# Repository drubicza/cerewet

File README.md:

# cerewet
Sound detector using LM358 Op-Amp

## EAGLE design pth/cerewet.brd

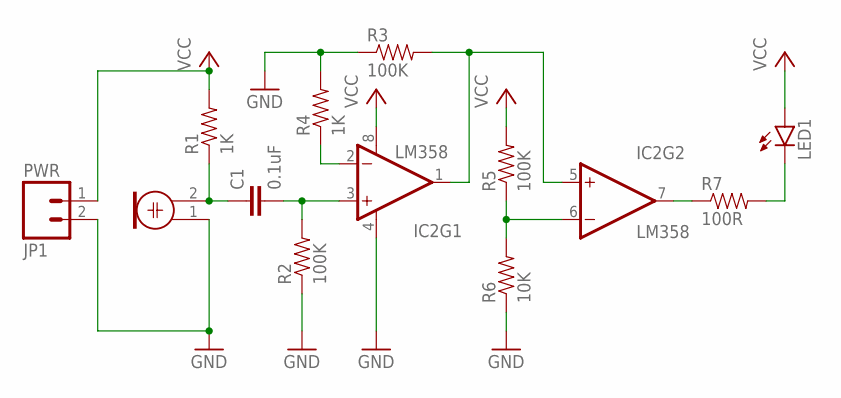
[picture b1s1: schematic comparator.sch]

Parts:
C1: 0.1uF; CAP-PTH-5MM
IC2: LM358; DIP08
JP1: PWR; 1X02_LONGPADS
LED1: LED5MM
MIC: ELECTRET_MICROPHON-WM-61B; WM-61B
R1, R4: 1K; AXIAL-0.3EZ
R2, R3, R5: 100K; AXIAL-0.3EZ
R6: 10K; AXIAL-0.3EZ
R7: 100R; AXIAL-0.3EZ

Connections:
GND: IC2.4 (V-), JP1.2, MIC.1, R2.P$1 (1), R3.P$1 (1), R4.P$2 (2), R6.P$1 (1)
unnamed: C1.1, MIC.2, R1.P$1 (1)
unnamed: C1.2, IC2.3 (+IN), R2.P$2 (2)
unnamed: IC2.2 (-IN), R4.P$1 (1)
unnamed: IC2.1 (OUT), IC2.5 (+IN), R3.P$2 (2)
unnamed: IC2.6 (-IN), R5.P$1 (1), R6.P$2 (2)
unnamed: IC2.7 (OUT), R7.P$1 (1)
unnamed: LED1.K (C), R7.P$2 (2)
VCC: IC2.8 (V+), JP1.1, LED1.A, R1.P$2 (2), R5.P$2 (2)

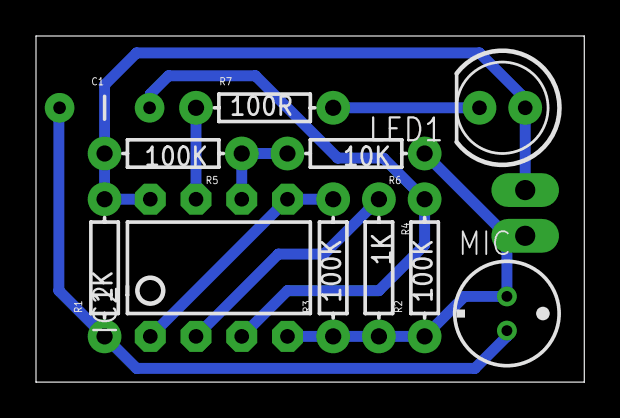
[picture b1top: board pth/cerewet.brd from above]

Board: 2 copper layers, 30.5 x 19.2 mm, 12 parts (0 on the bottom side), 9 nets.

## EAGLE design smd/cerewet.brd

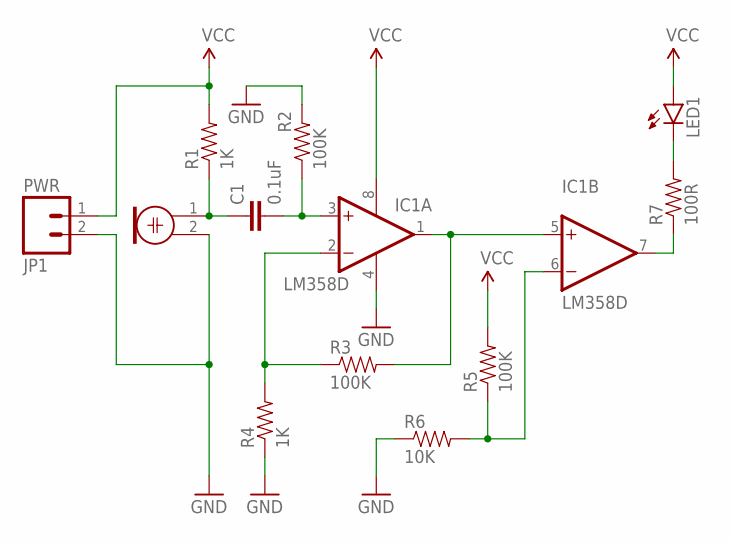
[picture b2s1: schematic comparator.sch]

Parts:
C1: 0.1uF; 0805
IC1: LM358D; SO08
JP1: PWR; 1X02
LED1: LED5MM
MIC: ELECTRET_MICROPHON-WM-61A; WM-61A
R1, R4: 1K; 0603-RES
R2, R3, R5: 100K; 0603-RES
R6: 10K; 0603-RES
R7: 100R; 0603-RES

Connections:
GND: IC1.4 (V-), JP1.2, MIC.2, R2.2, R4.1, R6.1
unnamed: C1.1, MIC.1, R1.1
unnamed: LED1.K (C), R7.2
unnamed: IC1.6 (-IN), R5.1, R6.2
unnamed: C1.2, IC1.3 (+IN), R2.1
unnamed: IC1.2 (-IN), R3.1, R4.2
unnamed: IC1.1 (OUT), IC1.5 (+IN), R3.2
unnamed: IC1.7 (OUT), R7.1
VCC: IC1.8 (V+), JP1.1, LED1.A, R1.2, R5.2

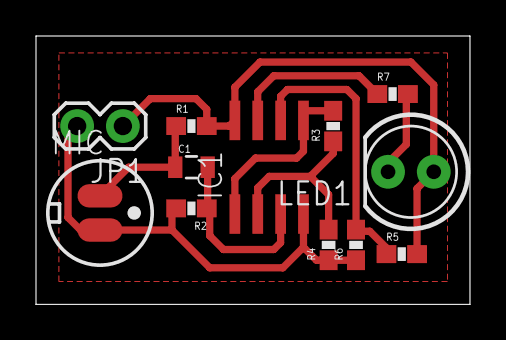
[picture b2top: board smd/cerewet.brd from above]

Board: 2 copper layers, 24.1 x 14.9 mm, 12 parts (0 on the bottom side), 9 nets.

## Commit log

2015-03-16 :loudspeaker: Initial commit

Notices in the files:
parts and their libraries:
SparkFun-AnalogIC: Licensing:Creative Commons ShareAlike 4.0 International - https://creativecommons.org/licenses/by-sa/4.0
